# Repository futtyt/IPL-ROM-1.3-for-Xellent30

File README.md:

# IPL-ROM 1.3 Patch for Xellent30

# 解説
IPL-ROM 1.3 Patch for Xellent30とは、Xellent30(s/PRO)を装着したX68000で利用するIPL-ROM 1.3へのパッチです。

このパッチを適用したIPL-ROM 1.3には以下の特徴があります。

【メリット】
* Xellent30の制御ツールであるch30.sysをSRAMに登録する必要がなくなる。
* デフォルトの動作CPUがMC68030になる。
* 起動画面表示中にXF2キー押下でMC68000へ、XF4キー押下でMC68030へ動作CPUを切替える。
* ソフトウェアリセット時はリセット前の動作CPUを維持する。
* SUPER、XVIでは内蔵SCSIも利用できる。(XVIはXellent30sで確認)

【プラマイゼロ？】
* 拡張SRAMの開始アドレスは$FC0000固定となり、IPL-ROMのアクセス先が拡張SRAMとなる。(拡張SRAMを自由に使えなくなりますが、IPL-ROMへのアクセスが若干早くなります。)

【デメリット】
* XT30DRV.Xなど、Xellent30用のツールを利用できなくなる。
* 内蔵SASIを利用できなくなる。

https://youtu.be/Bep6caA0rm4  
0:00 電源ON 030  
0:35 リセットボタン押下 030  
1:10 ソフトウェアリセット 030  
1:45 XF1キー押しながらリセットボタン押下 030→000  
2:18 ソフトウェアリセット 000  
2:48 リセットボタン押下 000→030  

# 動作実績
以下の構成で動作することを確認しています。
* X68000 PRO + Xellent30PRO + W27C512 x 2
* X68000 SUPER + Xellent30s + W27E010 x 2
* X68000 XVI + Xellent30s + W27E010 x 2

# 導入方法
1. 事前に以下のものを用意してください。
    * 各種ツール

        DB.X、dis.x、テキストマージツール、HAS.X、hlk.r、CV.X、bup.x

    * X68030のIPL-ROM $fe0000～$ffffff

        X68030実機にてDB.Xを起動して以下のコマンドを入力する。  
        ```-w IPLROM30Xel.DAT,fe0000 ffffff```

    * SCSI機の場合はX68030のROM30.DAT $fc0000～$fdffff

        X68030実機にてDB.Xを起動して以下のコマンドを入力する。  
        ```-w ROM30.DAT,fc0000 fdffff```

    * X68000のIPL-ROM $fe0000～$ffffff (6x12ドットフォント組込み用)

        X68000実機にてDB.Xを起動して以下のコマンドを入力する。  
        ```-w IPLROM.DAT,fe0000 ffffff```

    * UV-EPROM、EEPROM、FlashROM

        機種によって容量が異なります。  
        ACE、EXPERT、PROの場合は512Kbit(64K x 8bit、28pinDIP)  
        SUPER、XVIの場合は1Mbit(128K x 8bit、32pinDIP)  

        なお、SUPERのROMソケットは1MbitマスクROMを想定した28pinDIPですので、変換が必要です。  
        以下の図を参考にして結線してください。  

        水色　：隣同士を結線する。</br>
        灰色　：どこにも結線しない。</br>
        その他：同じ色同士を結線する。</br>
        試作基板のKiCADデータをROM28toEPROM32フォルダに格納しました。

    * ROMライタ(TL866II Plusなど)
    * X68000本体(Xellent30を装着可能な機種に限る)とXellent30

1. ROMイメージの生成
    1. ソースコードを利用する場合
        1. dis.xを以下のオプションで実行してソースコードを生成する。
            ※0.0.5からdisのオプションが変わりましたので注意してください。
            ```
            dis -zfe0000,ff0038 -q -m680x0 --overwrite -h IPLROM30Xel.DAT IPLROM30Xel.DAT.s
            ```
        1. テキストマージツールで本パッチを適用する。
        1. 添付のMakefileでソースコードをコンパイル、リンク、変換する。
            Makefileを利用しない場合は以下のコマンドを実行する。
            ```
            hlk.r -b0xfe0000 -oIPLROM30Xel.DAT.x IPLROM30Xel.DAT.o
            CV.X /rn IPLROM30Xel.DAT.x IPLROM30Xel.DAT.r
            REN IPLROM30Xel.DAT.r IPLROM30Xel.DAT
            ```
    1. バイナリ差分を利用する場合
        1. バイナリ差分ファイルを適用する。

1. 6x12ドットフォントの組込み
    1. 同梱のxfontconvine.exeを利用してIPLROM30Xel.DATにIPLROM.DAT内の6x12ドットフォントを組込みます。

1. ROMイメージの書込みと装着
    1. SCSI機の場合はROM30.DATとIPLROM30Xel.DATを結合する。
    1. ファイルをevenとoddに分割する。</br>
        XgproであればROMイメージを読み込む際のオプション設定を変更することで省略可能です。</br>
        </br>
        even:「Load mode」を「Load a low byte of a WORD(2 bytes)」にする。</br>
        odd:「Load mode」を「Load a high byte of a WORD(2 bytes)」にする。
    1. ROMライタで焼く。
    1. X68000に装着する。
        evenとodd、ROMの向きに注意して装着する。</br>
        ROM切替え用のディップスイッチを切替える。

(編集中...)

# 今後の野^H^H願望
* 030SYSPatchのROMパッチ部分を取り込む。
* IPL-ROM1.5に取り込まれる。(ォ

# 免責事項
このソフトウェア、およびドキュメントによって生じたいかなる損害も補償されません。

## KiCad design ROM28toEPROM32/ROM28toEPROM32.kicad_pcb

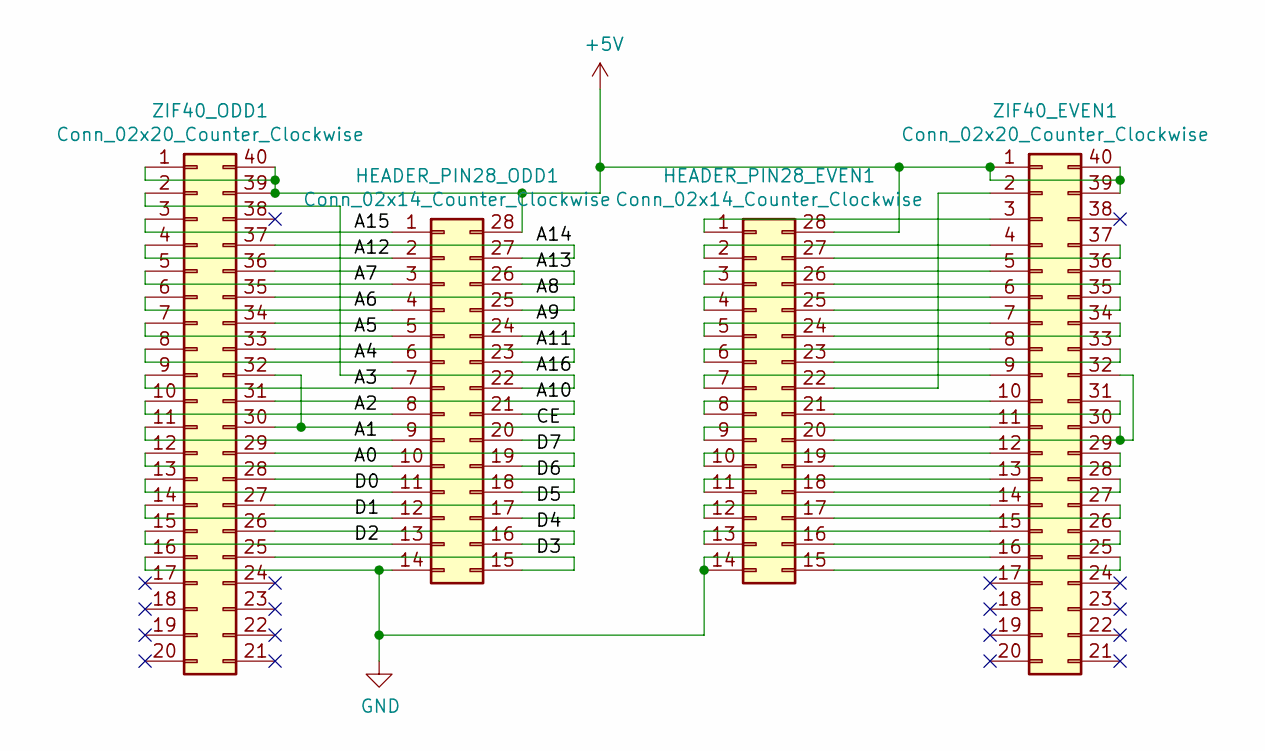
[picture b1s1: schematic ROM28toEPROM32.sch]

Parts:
HEADER_PIN28_EVEN1, HEADER_PIN28_ODD1: Conn_02x14_Counter_Clockwise; DIP-28_600
ZIF40_EVEN1, ZIF40_ODD1: Conn_02x20_Counter_Clockwise; DIP_Socket-40_W11.9_W12.7_W15.24_W17.78_W18.5_3M_240-1280-0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

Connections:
+5V: HEADER_PIN28_EVEN1.28, HEADER_PIN28_ODD1.28, ZIF40_EVEN1.1, ZIF40_EVEN1.39, ZIF40_EVEN1.40, ZIF40_ODD1.1, ZIF40_ODD1.39, ZIF40_ODD1.40
/A0: HEADER_PIN28_ODD1.10, ZIF40_ODD1.12
/A1: HEADER_PIN28_ODD1.9, ZIF40_ODD1.11
/A2: HEADER_PIN28_ODD1.8, ZIF40_ODD1.10
/A3: HEADER_PIN28_ODD1.7, ZIF40_ODD1.9
/A4: HEADER_PIN28_ODD1.6, ZIF40_ODD1.8
/A5: HEADER_PIN28_ODD1.5, ZIF40_ODD1.7
/A6: HEADER_PIN28_ODD1.4, ZIF40_ODD1.6
/A7: HEADER_PIN28_ODD1.3, ZIF40_ODD1.5
/A8: HEADER_PIN28_ODD1.25, ZIF40_ODD1.35
/A9: HEADER_PIN28_ODD1.24, ZIF40_ODD1.34
/A10: HEADER_PIN28_ODD1.21, ZIF40_ODD1.31
/A11: HEADER_PIN28_ODD1.23, ZIF40_ODD1.33
/A12: HEADER_PIN28_ODD1.2, ZIF40_ODD1.4
/A13: HEADER_PIN28_ODD1.26, ZIF40_ODD1.36
/A14: HEADER_PIN28_ODD1.27, ZIF40_ODD1.37
/A15: HEADER_PIN28_ODD1.1, ZIF40_ODD1.3
/A16: HEADER_PIN28_ODD1.22, ZIF40_ODD1.2
/CE: HEADER_PIN28_ODD1.20, ZIF40_ODD1.30, ZIF40_ODD1.32
/D0: HEADER_PIN28_ODD1.11, ZIF40_ODD1.13
/D1: HEADER_PIN28_ODD1.12, ZIF40_ODD1.14
/D2: HEADER_PIN28_ODD1.13, ZIF40_ODD1.15
/D3: HEADER_PIN28_ODD1.15, ZIF40_ODD1.25
/D4: HEADER_PIN28_ODD1.16, ZIF40_ODD1.26
/D5: HEADER_PIN28_ODD1.17, ZIF40_ODD1.27
/D6: HEADER_PIN28_ODD1.18, ZIF40_ODD1.28
/D7: HEADER_PIN28_ODD1.19, ZIF40_ODD1.29
GND: HEADER_PIN28_EVEN1.14, HEADER_PIN28_ODD1.14, ZIF40_EVEN1.16, ZIF40_ODD1.16
unnamed: HEADER_PIN28_EVEN1.1, ZIF40_EVEN1.3
unnamed: HEADER_PIN28_EVEN1.2, ZIF40_EVEN1.4
unnamed: HEADER_PIN28_EVEN1.3, ZIF40_EVEN1.5
unnamed: HEADER_PIN28_EVEN1.4, ZIF40_EVEN1.6
unnamed: HEADER_PIN28_EVEN1.5, ZIF40_EVEN1.7
unnamed: HEADER_PIN28_EVEN1.6, ZIF40_EVEN1.8
unnamed: HEADER_PIN28_EVEN1.7, ZIF40_EVEN1.9
unnamed: HEADER_PIN28_EVEN1.8, ZIF40_EVEN1.10
unnamed: HEADER_PIN28_EVEN1.9, ZIF40_EVEN1.11
unnamed: HEADER_PIN28_EVEN1.10, ZIF40_EVEN1.12
unnamed: HEADER_PIN28_EVEN1.11, ZIF40_EVEN1.13
unnamed: HEADER_PIN28_EVEN1.12, ZIF40_EVEN1.14
unnamed: HEADER_PIN28_EVEN1.13, ZIF40_EVEN1.15
unnamed: HEADER_PIN28_EVEN1.15, ZIF40_EVEN1.25
unnamed: HEADER_PIN28_EVEN1.16, ZIF40_EVEN1.26
unnamed: HEADER_PIN28_EVEN1.17, ZIF40_EVEN1.27
unnamed: HEADER_PIN28_EVEN1.18, ZIF40_EVEN1.28
unnamed: HEADER_PIN28_EVEN1.19, ZIF40_EVEN1.29
unnamed: HEADER_PIN28_EVEN1.20, ZIF40_EVEN1.30, ZIF40_EVEN1.32
unnamed: HEADER_PIN28_EVEN1.21, ZIF40_EVEN1.31
unnamed: HEADER_PIN28_EVEN1.22, ZIF40_EVEN1.2
unnamed: HEADER_PIN28_EVEN1.23, ZIF40_EVEN1.33
unnamed: HEADER_PIN28_EVEN1.24, ZIF40_EVEN1.34
unnamed: HEADER_PIN28_EVEN1.25, ZIF40_EVEN1.35
unnamed: HEADER_PIN28_EVEN1.26, ZIF40_EVEN1.36
unnamed: HEADER_PIN28_EVEN1.27, ZIF40_EVEN1.37

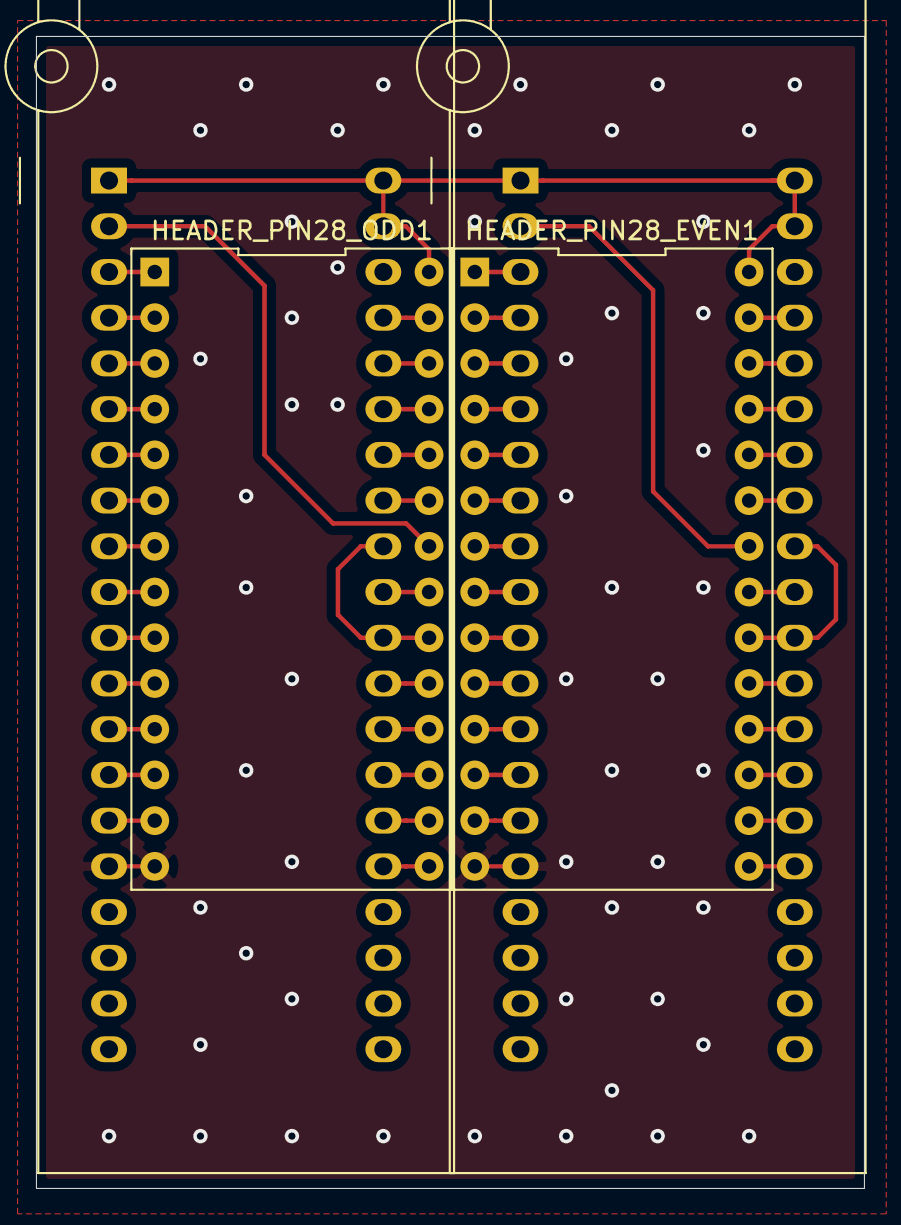
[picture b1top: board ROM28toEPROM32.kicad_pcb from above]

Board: 2 copper layers, 46.0 x 64.0 mm, 4 parts (0 on the bottom side), 54 nets.

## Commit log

2021-03-02 0.0.1 commit.
2021-03-03 0.0.1 bfd
2021-03-04 0.0.2 Xellent30未装着時にRESETしていない不具合を修正しました。
2021-03-20 0.0.3
2021-07-03 0.0.4 CPUモード切替手段を変更しました。 起動画面表示中にXF2キー押下でMC68000へ、XF4キー押下でMC68030へ動作CPUを切替えます。
2021-07-15 ROM28toEPROM32を追加しました。
2022-04-02 0.0.5 SCSIのソフトウェア転送でアドレスエラーが発生する不具合を修正しました。 6x12ドットフォントに対応しました。
